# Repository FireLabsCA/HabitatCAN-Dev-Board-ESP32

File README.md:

# HabitatCAN Dev Board (ESP32)

A development board designed for HabitatCAN home automation applications, featuring an ESP32-C3-MINI-1 microcontroller with integrated CAN bus transceiver and comprehensive I/O capabilities.

## Overview

The HabitatCAN Dev Board is a development platform for building HabitatCAN-compatible devices. HabitatCAN is an open standard for home automation built on the Controller Area Network (CAN) bus, providing reliable, low-latency communication between sensors, switches, actuators, and controllers in residential and light commercial environments.

Unlike proprietary systems (Control4, KNX, Zigbee), HabitatCAN is designed to be open, inexpensive, and implementable on common microcontrollers. It leverages structured cabling (Ethernet Cat5e/Cat6) for wiring but uses CAN signaling rather than Ethernet, allowing for robust operation in electrically noisy environments and over long distances.

## What is HabitatCAN?

HabitatCAN is a local-first home automation standard that provides:

- **Reliable Communication**: CAN bus ensures robust, real-time communication over structured cabling
- **Local-First Design**: Homes continue to function without Internet or cloud connectivity
- **Fault Isolation**: Failures are isolated and recovered automatically
- **Simple Devices**: Minimal logic in devices, complexity handled by controllers
- **Extensibility**: New device types and commands can be added without breaking older firmware

### Key Features of HabitatCAN:
- **500 kbit/s CAN bus** over Cat5e/Cat6 cabling (~100m reach)
- **24V courtesy power** distributed over structured cabling
- **Hierarchical addressing**: NetworkID (16-bit) + RoomID (8-bit) + NodeID (8-bit)
- **Automatic device discovery** and commissioning
- **Group and scene support** for complex automation
- **Fault tolerance** with backup controllers and local autonomy

## Board Images

%20-%20Image%20-%20Side%201.png)

%20-%20Image%20-%20Front.png)

%20-%20Image%20-%20Back.png)

## Key Features

### Microcontroller
- **ESP32-C3-MINI-1**: Ultra-low-power MCU with 2.4 GHz Wi-Fi and Bluetooth Low Energy
- **RISC-V 32-bit single-core processor**
- **400 KB SRAM, 384 KB ROM**
- **Built-in Wi-Fi and Bluetooth connectivity**

### CAN Bus Interface
- **TJA1051T CAN Transceiver**: High-speed CAN transceiver with silent mode
- **RJ45 Connector**: Standard Ethernet-style connector for HabitatCAN network connection
- **HabitatCAN Compliant**: Follows HabitatCAN specification for structured cabling

### Power Management
- **USB-C Power Input**: 5V input via USB-C connector
- **24V Input Support**: Optional 24V input with step-down conversion

### I/O Capabilities
- **18-pin GPIO Header**: All ESP32-C3 GPIO pins accessible
- **Serial Communication**: UART0 (TX/RX) pins available
- **ADC Channels**: Multiple analog input channels
- **Boot/Reset Controls**: Dedicated boot and reset buttons
- **Status LED**: Built-in status indicator
- **USB-C Programming**: Direct programming via USB-C

## Pinout

### GPIO Header (J1)
| Pin | Function | Description |
|-----|----------|-------------|
| 1   | GND      | Ground      |
| 2   | 3V3      | 3.3V Power  |
| 3   | GPIO0    | GPIO0 / Boot |
| 4   | GPIO1    | GPIO1 |
| 5   | GPIO2    | GPIO2 |
| 6   | GPIO3    | GPIO3 |
| 7   | GPIO4    | GPIO4 / CAN RX |
| 8   | GPIO5    | GPIO5 / CAN TX |
| 9   | GPIO6    | GPIO6 |
| 10  | GPIO7    | GPIO7 |
| 11  | GPIO8    | GPIO8 / Status LED |
| 12  | GPIO9    | GPIO9 |
| 13  | GPIO10   | GPIO10 |
| 14  | S_TX     | Serial TX |
| 15  | S_RX     | Serial RX |
| 16  | EN       | Enable / Reset |
| 17  | 5V       | 5V Power |
| 18  | GND      | Ground |

### CAN Bus Connector (J3) - HabitatCAN Compliant
| Pin | Function | Description |
|-----|----------|-------------|
| 1   | GND      | Ground |
| 2   | GND      | Ground |
| 3   | CAN_H    | CAN High |
| 4   | +24V     | 24V Courtesy Power |
| 5   | +24V     | 24V Courtesy Power |
| 6   | CAN_L    | CAN Low |
| 7   | Reserved | Reserved for future use |
| 8   | Reserved | Reserved for future use |

### I2C Connector (J6) - QWIIC Compliant
| Pin | Function | Description |
|-----|----------|-------------|
| 1   | GND      | Ground |
| 1   | 3V3      | 3.3V Power |
| 1   | SDA      | Serial Data |
| 1   | SCL      | Serial Clock |

## HabitatCAN Development

### Device Types
This development board can be used to create various HabitatCAN device types:

**Sensors:**
- Door/Window sensors
- Motion sensors  
- Temperature sensors
- CO₂ sensors
- Humidity sensors
- Light sensors

**Switches:**
- Light switches
- Scene switches
- Dimmer controls

**Actuators:**
- Relay/Outlet controllers
- Dimmer controllers
- Blind controllers
- RGB/CCT lighting controllers

### HabitatCAN Protocol
The board implements the HabitatCAN protocol with:
- **Device Discovery**: Automatic UID-based device identification
- **Address Assignment**: RoomID/NodeID assignment by Room Controllers
- **Message Types**: FAULT, DISCOVER, ASSIGN, HEARTBEAT, COMMAND, GROUP, TELEMETRY
- **Security**: HMAC authentication for critical frames
- **Group/Scene Support**: Integration with HabitatCAN automation

## Getting Started

### Prerequisites
- Arduino IDE with ESP32 board support, or
- PlatformIO, or
- ESP-IDF development framework
- USB-C cable for programming and power
- HabitatCAN network infrastructure (Room Controller, Main Controller)

### Programming
1. Connect the board to your computer via USB-C
2. Install the ESP32 board package in your development environment
3. Select the ESP32-C3 board variant
4. Upload your HabitatCAN-compatible firmware

### HabitatCAN Network Setup
1. Connect the RJ45 connector to your HabitatCAN network
2. Ensure proper termination (automatic if used as end device)
3. The device will automatically discover and request address assignment
4. Configure device type and capabilities in your firmware

## Hardware Design

### Schematic
The board design is available in KiCad format in the `cad/` directory:
- Main schematic: `HabitatCAN Dev Board (ESP32).kicad_sch`
- PCB layout: `HabitatCAN Dev Board (ESP32).kicad_pcb`

### Manufacturing Files
Gerber files for PCB manufacturing are available in the `cad/Gerber/` directory:
- Copper layers (F_Cu, B_Cu)
- Solder mask (F_Mask, B_Mask)
- Silkscreen (F_Silkscreen, B_Silkscreen)
- Solder paste (F_Paste, B_Paste)
- Drill files (PTH.drl, NPTH.drl)

### Panel Design
A panelized version is available for batch manufacturing in the `cad/Panel/` directory.

## Revision History

- **Rev 4 (2025-09-15)**: Added QWIIC interface
- **Rev 3 (2025-09-14)**: Cleaned up bugs and silkscreen layer (archived in `cad/Rev3/`)
- **Rev 2**: Previous revision (archived in `cad/Rev2/`)
- **Rev 1**: Initial design

## License

This project is licensed under the Creative Commons Attribution-ShareAlike 4.0 International License. See `LICENSE.md` for details.

## Contributing

Contributions are welcome! Please feel free to submit issues, feature requests, or pull requests.

## Support

For questions and support, please open an issue in this repository.

---

*This development board is designed for HabitatCAN home automation development. Always follow proper safety guidelines when working with electrical circuits and home automation systems.*

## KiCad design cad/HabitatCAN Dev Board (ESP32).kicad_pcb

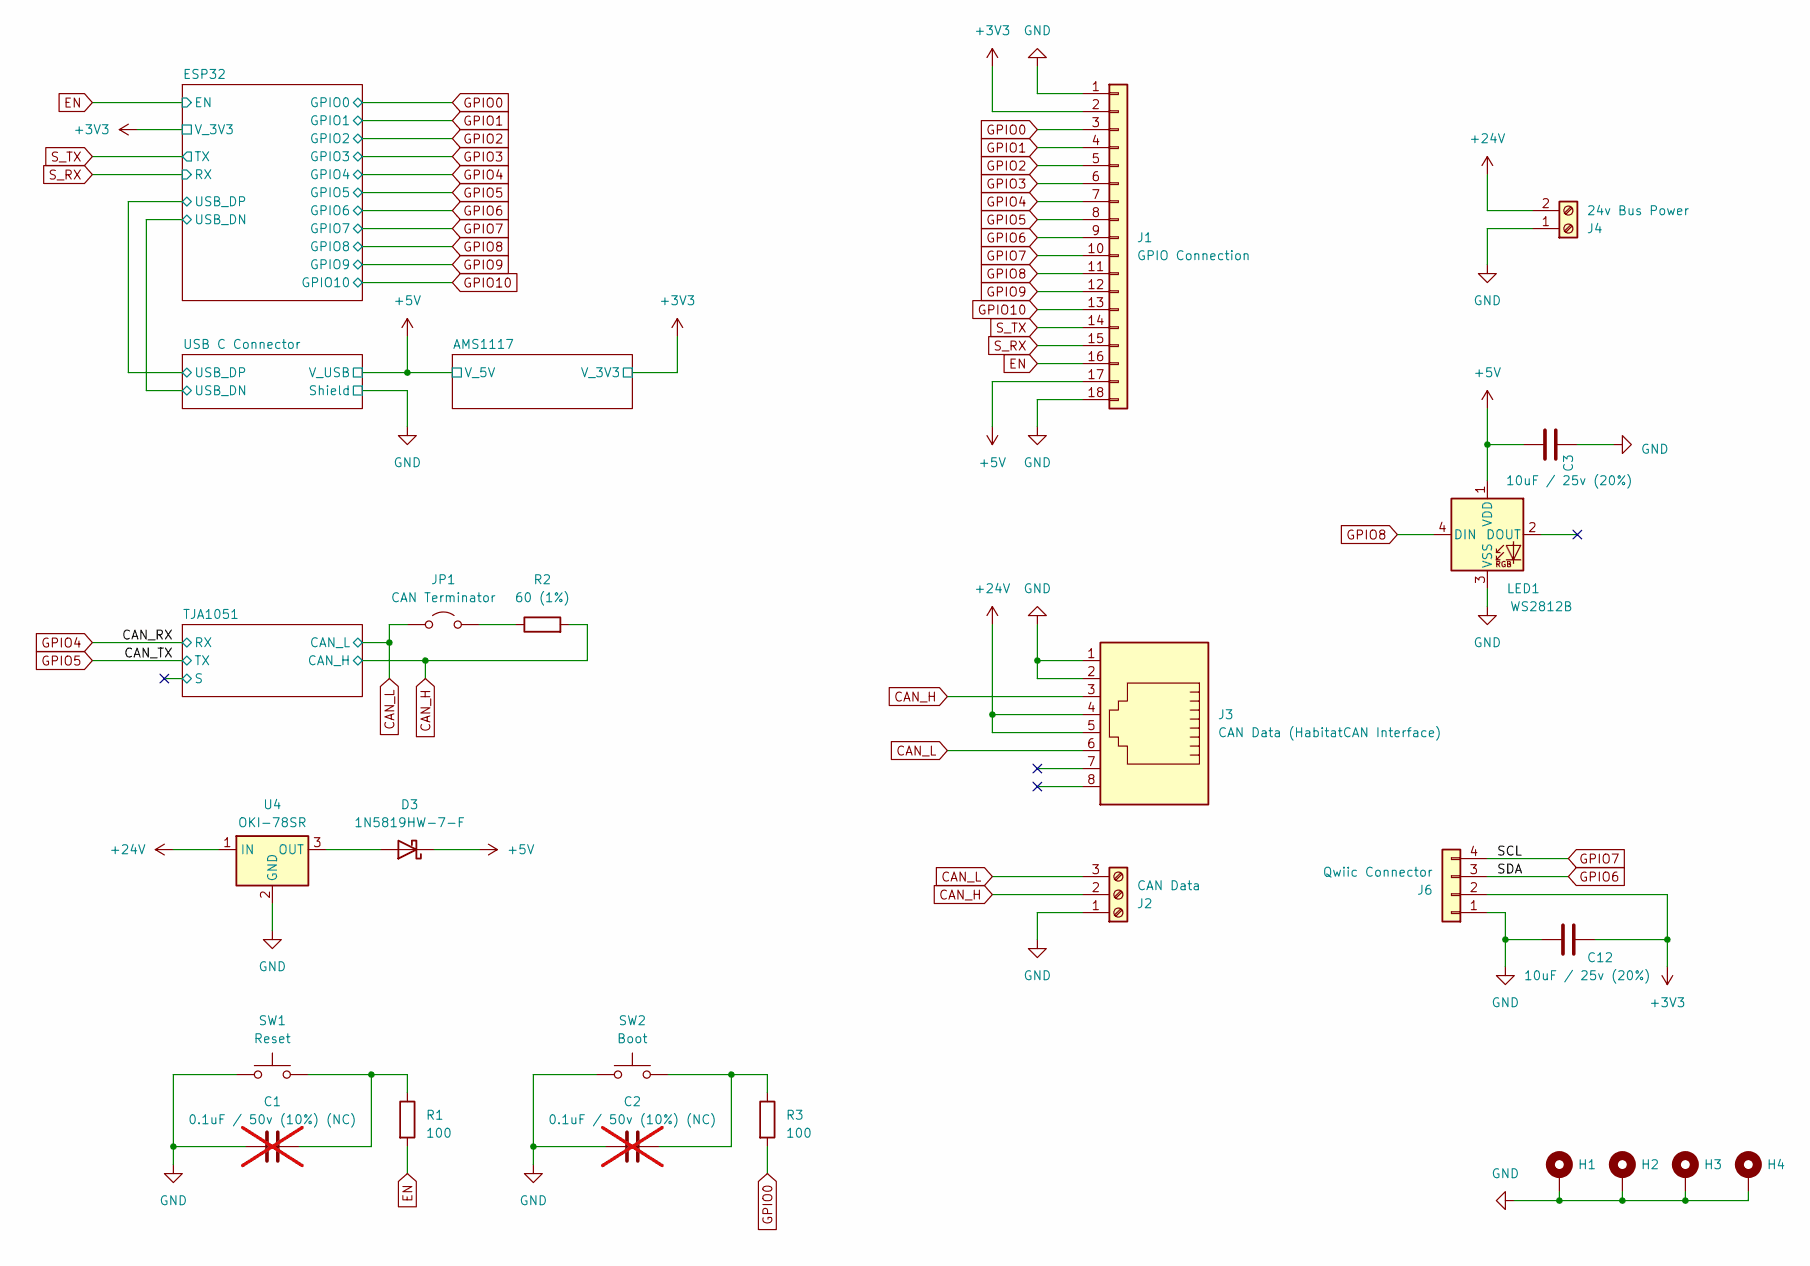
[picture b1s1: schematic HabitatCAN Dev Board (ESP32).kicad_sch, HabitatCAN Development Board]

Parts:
C1, C2: 0.1uF / 50v (10%) (NC); C_0603_1608Metric; not fitted
C3, C12: 10uF / 25v (20%); C_0603_1608Metric
D3: 1N5819HW-7-F; D_SOD-123; DigiKey 1N5819HW-FDICT-ND
H1, H2, H3, H4: MountingHole_Pad; MountingHole_3.2mm_M3_Pad_Via
J1: GPIO Connection; PinHeader_1x18_P2.54mm_Vertical
J2: CAN Data; TerminalBlock_MaiXu_MX126-5.0-03P_1x03_P5.00mm
J3: CAN Data (HabitatCAN Interface); RJ45_Amphenol_54602-x08_Horizontal
J4: 24v Bus Power; TerminalBlock_MaiXu_MX126-5.0-02P_1x02_P5.00mm
J6: Qwiic Connector; JST_SH_BM04B-SRSS-TB_1x04-1MP_P1.00mm_Vertical
JP1: CAN Terminator; PinHeader_1x02_P2.54mm_Vertical
LED1: WS2812B; LED_WS2812B_PLCC4_5.0x5.0mm_P3.2mm
R1, R3: 100; R_0603_1608Metric; DigiKey RMCF0603JT5K10CT-ND
R2: 60 (1%); R_0603_1608Metric
SW1: Reset; SW_Tactile_SPST_NO_Straight_CK_PTS636Sx25SMTRLFS
SW2: Boot; SW_Tactile_SPST_NO_Straight_CK_PTS636Sx25SMTRLFS
U4: OKI-78SR; Converter_DCDC_Murata_OKI-78SR_Horizontal

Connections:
+3V3: C12.2, J1.2, J6.2; also elsewhere on the board
+5V: C3.1, D3.1 (K), J1.17, LED1.1 (VDD); also elsewhere on the board
+24V: J3.4, J3.5, J4.2, U4.1 (IN)
CAN_H: J2.2, J3.3, R2.2; also elsewhere on the board
CAN_L: J2.3, J3.6, JP1.1 (A); also elsewhere on the board
EN: J1.16, R1.2; also elsewhere on the board
GND: C1.1, C2.1, C3.2, C12.1, H1.1, H2.1, H3.1, H4.1, J1.1, J1.18, J2.1, J3.1, J3.2, J4.1, J6.1, LED1.3 (VSS), SW1.1, SW2.1, U4.2 (GND); also elsewhere on the board
GPIO0: J1.3, R3.2; also elsewhere on the board
GPIO1: J1.4; also elsewhere on the board
GPIO2: J1.5; also elsewhere on the board
GPIO3: J1.6; also elsewhere on the board
GPIO4: J1.7; also elsewhere on the board
GPIO5: J1.8; also elsewhere on the board
GPIO6: J1.9, J6.3; also elsewhere on the board
GPIO7: J1.10, J6.4; also elsewhere on the board
GPIO8: J1.11, LED1.4 (DIN); also elsewhere on the board
GPIO9: J1.12; also elsewhere on the board
GPIO10: J1.13; also elsewhere on the board
unnamed: C1.2, R1.1, SW1.2
unnamed: C2.2, R3.1, SW2.2
unnamed: D3.2 (A), U4.3 (OUT)
unnamed: JP1.2 (B), R2.1
S_RX: J1.15; also elsewhere on the board
S_TX: J1.14; also elsewhere on the board

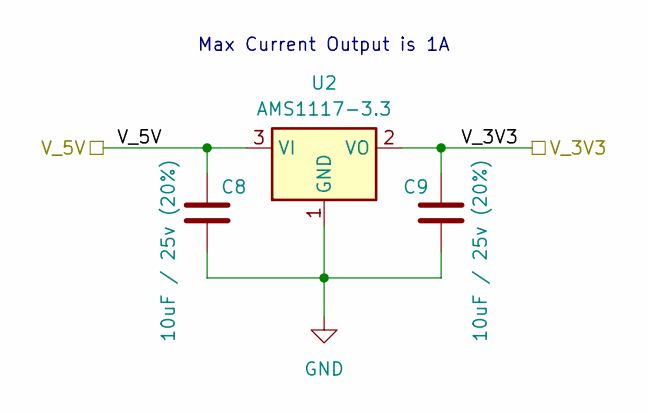
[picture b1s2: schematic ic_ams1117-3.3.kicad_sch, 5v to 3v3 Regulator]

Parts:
C8, C9: 10uF / 25v (20%); C_0603_1608Metric; DigiKey 1276-1869-1-ND
U2: AMS1117-3.3; SOT-223-3_TabPin2; DigiKey 4518-AMS1117CD-3.3CT-ND

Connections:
+3V3: C9.1, U2.2 (VO); also elsewhere on the board
+5V: C8.1, U2.3 (VI); also elsewhere on the board
GND: C8.2, C9.2, U2.1 (GND); also elsewhere on the board

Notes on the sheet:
Max Current Output is 1A

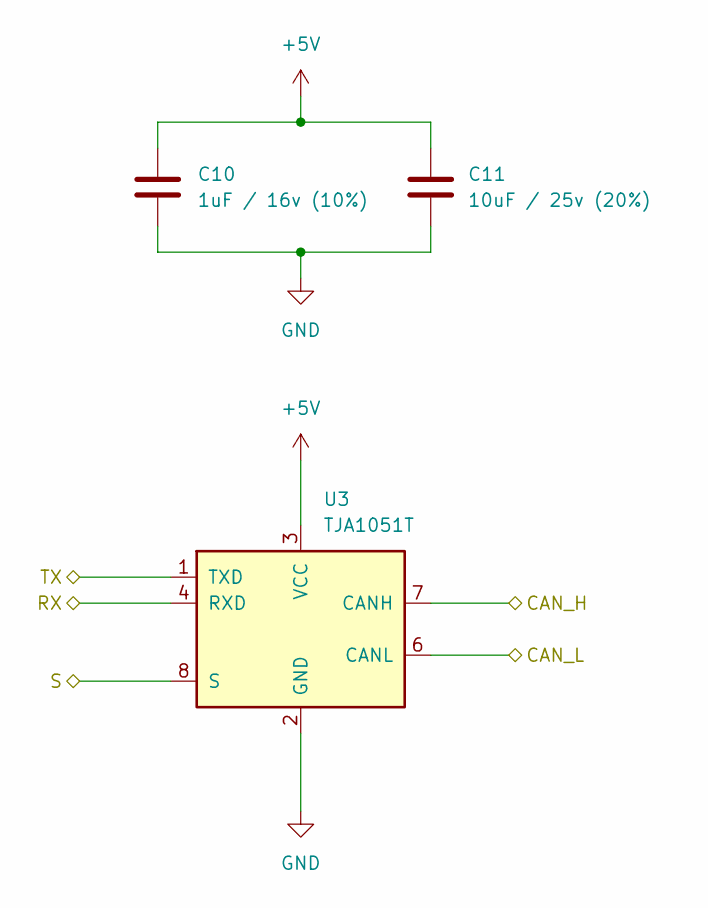
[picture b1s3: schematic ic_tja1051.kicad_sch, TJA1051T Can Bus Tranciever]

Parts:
C10: 1uF / 16v (10%); C_0603_1608Metric
C11: 10uF / 25v (20%); C_0603_1608Metric; DigiKey 1276-1869-1-ND
U3: TJA1051T; SOIC-8_3.9x4.9mm_P1.27mm

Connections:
+5V: C10.1, C11.1, U3.3 (VCC); also elsewhere on the board
/TJA1051/S: U3.8 (S)
CAN_H: U3.7 (CANH); also elsewhere on the board
CAN_L: U3.6 (CANL); also elsewhere on the board
GND: C10.2, C11.2, U3.2 (GND); also elsewhere on the board
GPIO4: U3.4 (RXD); also elsewhere on the board
GPIO5: U3.1 (TXD); also elsewhere on the board

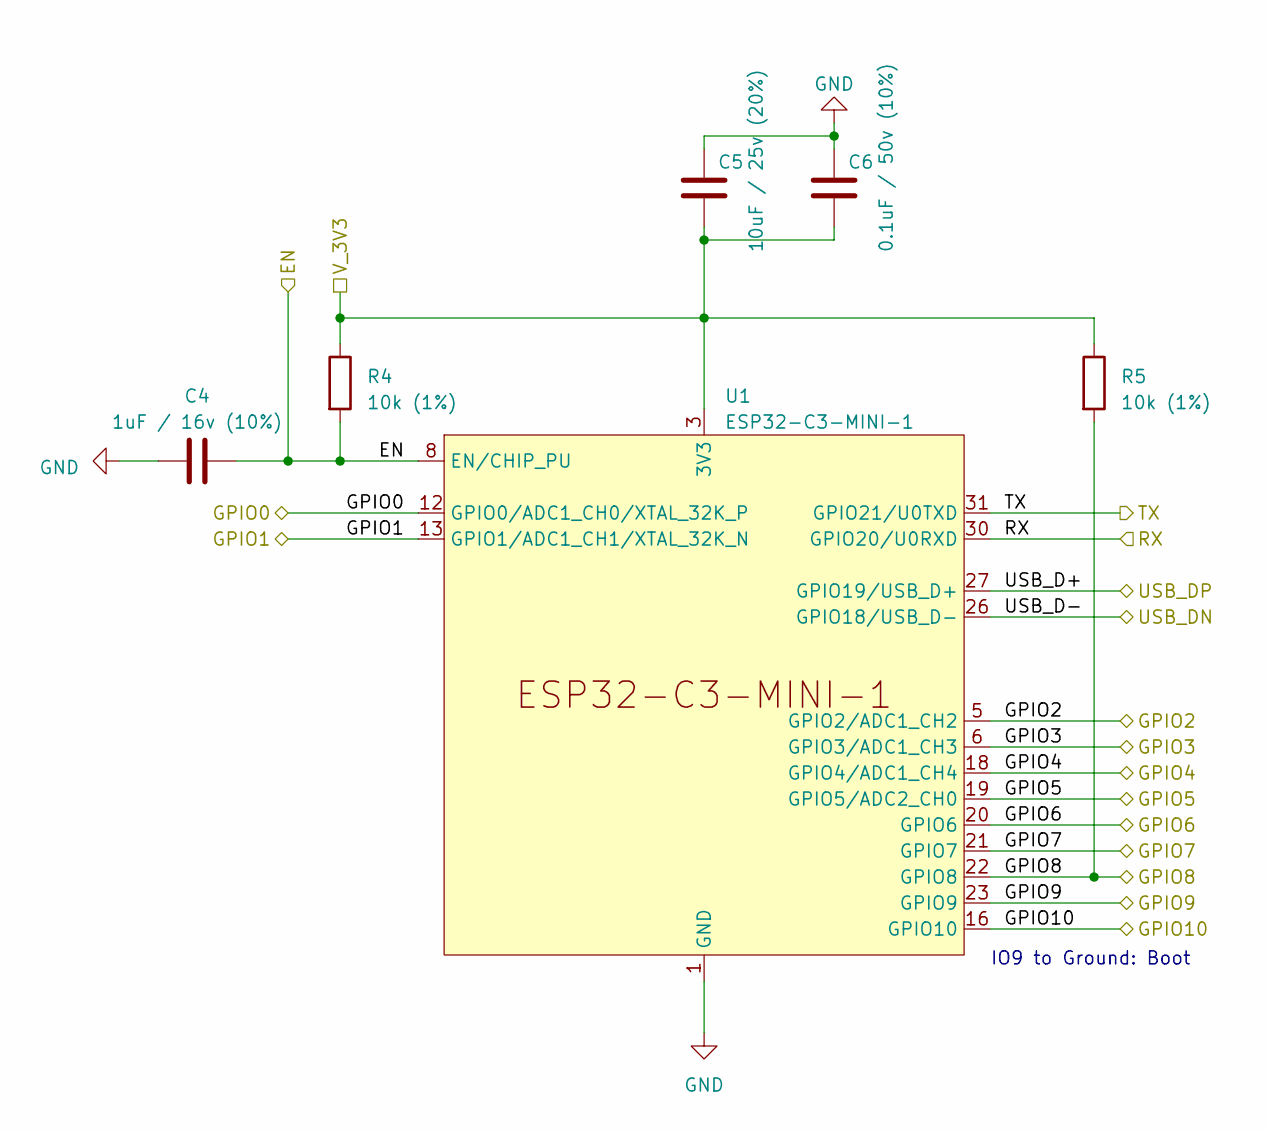
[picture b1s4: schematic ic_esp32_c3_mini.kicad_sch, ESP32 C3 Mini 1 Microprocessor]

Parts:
C4: 1uF / 16v (10%); C_0603_1608Metric
C5: 10uF / 25v (20%); C_0603_1608Metric
C6: 0.1uF / 50v (10%); C_0603_1608Metric
R4, R5: 10k (1%); R_0603_1608Metric
U1: ESP32-C3-MINI-1

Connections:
+3V3: C5.1, C6.1, R4.1, R5.1, U1.3 (3V3); also elsewhere on the board
/ESP32/USB_D+: U1.27 (GPIO19/USB_D+); also elsewhere on the board
/ESP32/USB_D-: U1.26 (GPIO18/USB_D-); also elsewhere on the board
EN: C4.2, R4.2, U1.8 (EN/CHIP_PU); also elsewhere on the board
GND: C4.1, C5.2, C6.2, U1.1 (GND), U1.2 (GND), U1.11 (GND), U1.14 (GND), U1.36 (GND), U1.37 (GND), U1.38 (GND), U1.39 (GND), U1.40 (GND), U1.41 (GND), U1.42 (GND), U1.43 (GND), U1.44 (GND), U1.45 (GND), U1.46 (GND), U1.47 (GND), U1.48 (GND), U1.49 (GND), U1.50 (GND), U1.51 (GND), U1.52 (GND), U1.53 (GND); also elsewhere on the board
GPIO0: U1.12 (GPIO0/ADC1_CH0/XTAL_32K_P); also elsewhere on the board
GPIO1: U1.13 (GPIO1/ADC1_CH1/XTAL_32K_N); also elsewhere on the board
GPIO2: U1.5 (GPIO2/ADC1_CH2); also elsewhere on the board
GPIO3: U1.6 (GPIO3/ADC1_CH3); also elsewhere on the board
GPIO4: U1.18 (GPIO4/ADC1_CH4); also elsewhere on the board
GPIO5: U1.19 (GPIO5/ADC2_CH0); also elsewhere on the board
GPIO6: U1.20 (GPIO6); also elsewhere on the board
GPIO7: U1.21 (GPIO7); also elsewhere on the board
GPIO8: R5.2, U1.22 (GPIO8); also elsewhere on the board
GPIO9: U1.23 (GPIO9); also elsewhere on the board
GPIO10: U1.16 (GPIO10); also elsewhere on the board
S_RX: U1.30 (GPIO20/U0RXD); also elsewhere on the board
S_TX: U1.31 (GPIO21/U0TXD); also elsewhere on the board

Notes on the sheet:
IO9 to Ground: Boot

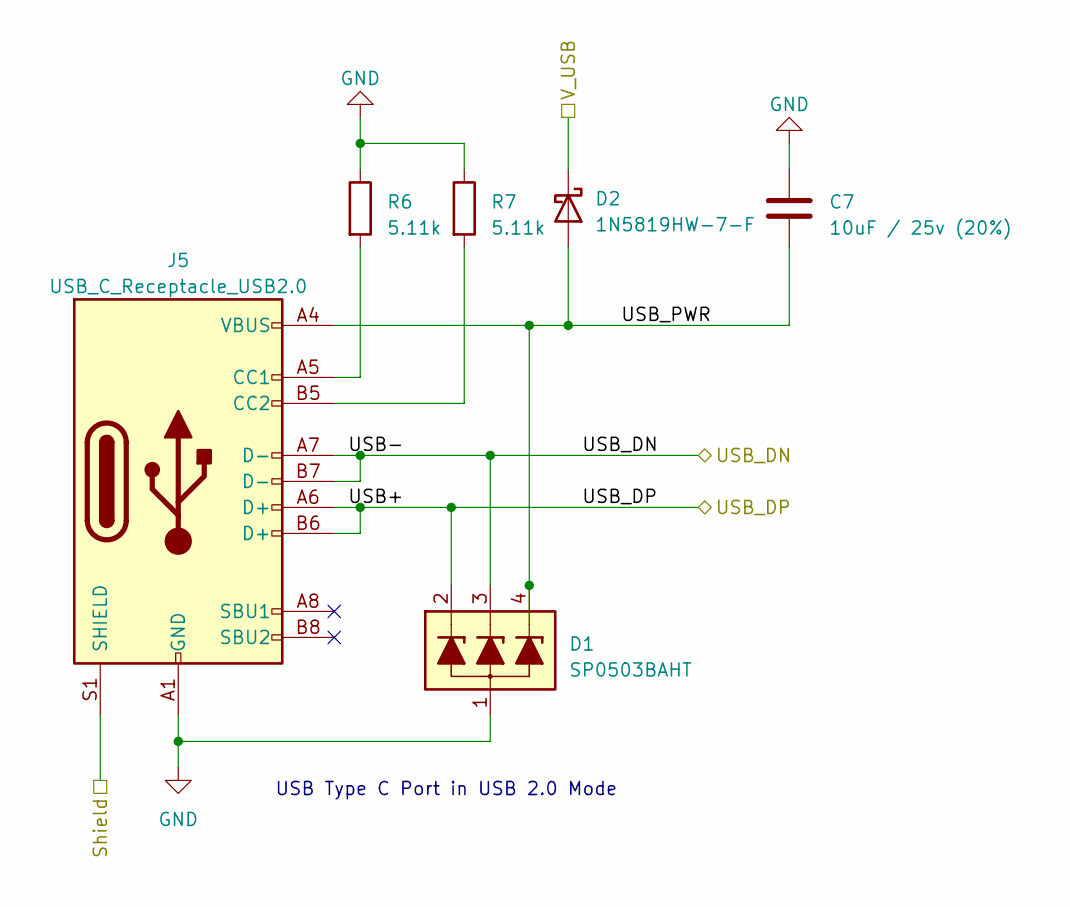
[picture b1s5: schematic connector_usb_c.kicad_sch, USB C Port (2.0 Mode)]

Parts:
C7: 10uF / 25v (20%); C_0603_1608Metric; DigiKey 1276-1869-1-ND
D1: SP0503BAHT; SOT-143
D2: 1N5819HW-7-F; D_SOD-123; DigiKey 1N5819HW-FDICT-ND
J5: USB_C_Receptacle_USB2.0; USB_C_Receptacle_GCT_USB4105-xx-A_16P_TopMnt_Horizontal; DigiKey 2073-USB4105-GF-ACT-ND
R6, R7: 5.11k; R_0603_1608Metric; DigiKey RMCF0603JT5K10CT-ND

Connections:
+5V: D2.1 (K); also elsewhere on the board
/ESP32/USB_D+: D1.2 (L1), J5.A6 (D+), J5.B6 (D+); also elsewhere on the board
/ESP32/USB_D-: D1.3 (L2), J5.A7 (D-), J5.B7 (D-); also elsewhere on the board
/USB C Connector/USB_PWR: C7.1, D1.4 (L3), D2.2 (A), J5.A4 (VBUS), J5.A9 (VBUS), J5.B4 (VBUS), J5.B9 (VBUS)
GND: C7.2, D1.1 (VN), J5.A1 (GND), J5.A12 (GND), J5.B1 (GND), J5.B12 (GND), J5.S1 (SHIELD), R6.1, R7.1; also elsewhere on the board
unnamed: J5.A5 (CC1), R6.2
unnamed: J5.B5 (CC2), R7.2

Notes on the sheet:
USB Type C Port in USB 2.0 Mode

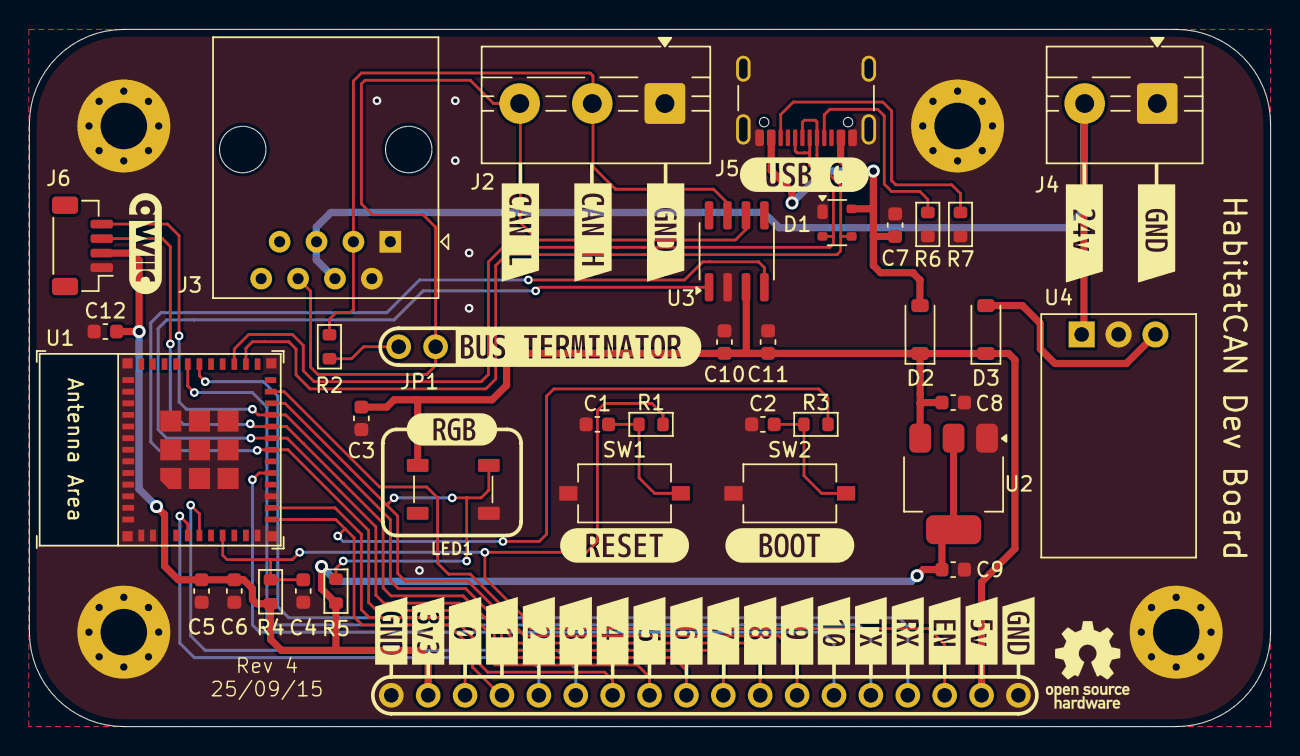
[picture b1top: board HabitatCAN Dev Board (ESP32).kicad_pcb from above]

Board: 2 copper layers, 85.5 x 48.0 mm, 68 parts (0 on the bottom side), 29 nets.

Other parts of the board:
kibuzzard-68C5BCFF: G***; kibuzzard-68C5BCFF
kibuzzard-68C5BDE3: G***; kibuzzard-68C5BDE3
kibuzzard-68C5C7D3: G***; kibuzzard-68C5C7D3
kibuzzard-68C5C7EB: G***; kibuzzard-68C5C7EB
kibuzzard-68C5C8AB: G***; kibuzzard-68C5C8AB
kibuzzard-68C5C8C1: G***; kibuzzard-68C5C8C1
kibuzzard-68C5C8CC: G***; kibuzzard-68C5C8CC
kibuzzard-68C5C8DC: G***; kibuzzard-68C5C8DC
kibuzzard-68C5C8ED: G***; kibuzzard-68C5C8ED
kibuzzard-68C5C8FB: G***; kibuzzard-68C5C8FB
kibuzzard-68C5C81E: G***; kibuzzard-68C5C81E
kibuzzard-68C5C82A: G***; kibuzzard-68C5C82A
kibuzzard-68C5C84A: G***; kibuzzard-68C5C84A
kibuzzard-68C5C89F: G***; kibuzzard-68C5C89F
kibuzzard-68C5C90A: G***; kibuzzard-68C5C90A
kibuzzard-68C5C857: G***; kibuzzard-68C5C857
kibuzzard-68C5C878: G***; kibuzzard-68C5C878
kibuzzard-68C5C890: G***; kibuzzard-68C5C890
kibuzzard-68C5C916: G***; kibuzzard-68C5C916
kibuzzard-68C35A34: G***; kibuzzard-68C35A34
kibuzzard-68C35C66: G***; kibuzzard-68C35C66
kibuzzard-68C35D4D: G***; kibuzzard-68C35D4D
kibuzzard-68C35D6E: G***; kibuzzard-68C35D6E
kibuzzard-68C35D54, kibuzzard-68C35D54#2: G***; kibuzzard-68C35D54
kibuzzard-68C366C1: G***; kibuzzard-68C366C1
kibuzzard-68C366CA: G***; kibuzzard-68C366CA
kibuzzard-68C36393: G***; kibuzzard-68C36393

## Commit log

2025-09-14 initial upload
2025-09-14 added rendered images of the board
2025-09-16 Updated to Rev4
